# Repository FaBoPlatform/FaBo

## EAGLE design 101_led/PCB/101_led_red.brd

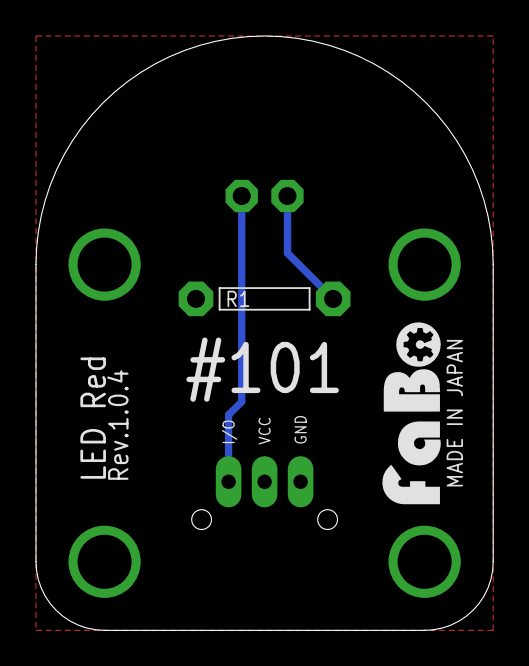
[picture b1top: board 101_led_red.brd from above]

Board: 2 copper layers, 25.4 x 33.0 mm, 5 parts (0 on the bottom side), 3 nets.

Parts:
J1: FABO_BRICK_3PIN
LED1: LED_5MM
R1: 1k; AXL-REGULAR
U$1: LOGO_FABO_MS
U$2: LOGO_OSHW_M_BOTTOM

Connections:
GND: J1.GND, R1.1
unnamed: J1.I/O, LED1.A
unnamed: LED1.K, R1.2

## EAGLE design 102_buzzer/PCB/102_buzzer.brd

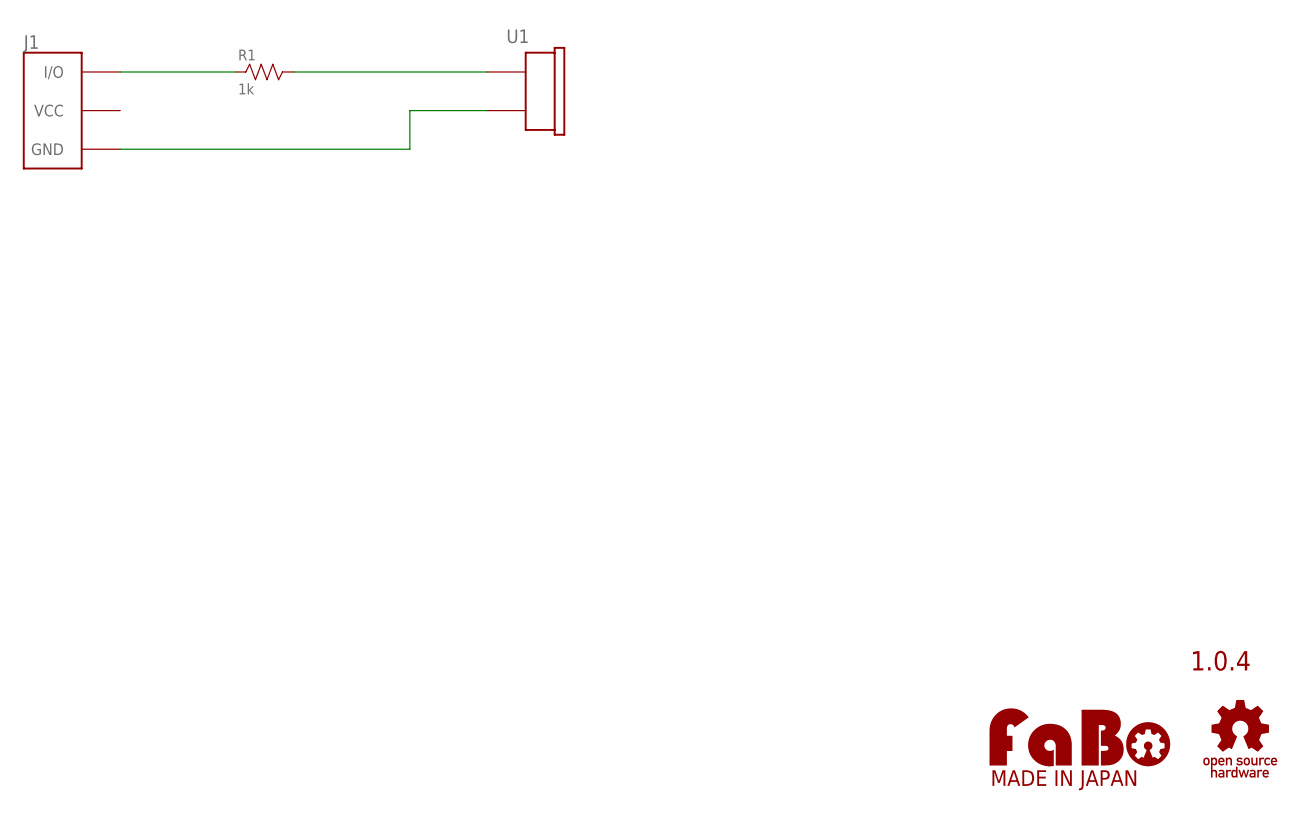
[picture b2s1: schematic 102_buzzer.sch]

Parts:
J1: FABO_BRICK_3PIN
R1: 1k; AXL-REGULAR
U1: BUZZER; PKM13EPYH4000-A0
U$2: LOGO_FABO-M; LOGO_FABO_MS
U$3: LOGO_OSHW-M_BOTTOM; LOGO_OSHW_M_BOTTOM

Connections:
GND: J1.GND, U1.2
unnamed: J1.I/O, R1.1
unnamed: R1.2, U1.1

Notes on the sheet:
1.0.4

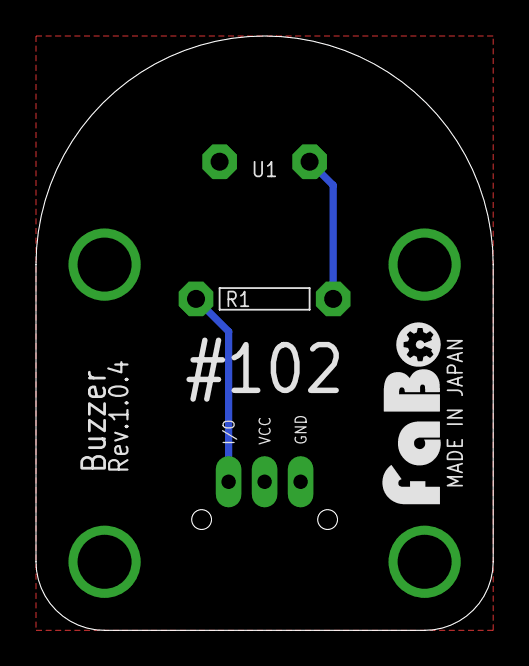
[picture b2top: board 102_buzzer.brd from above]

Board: 2 copper layers, 25.4 x 33.0 mm, 5 parts (0 on the bottom side), 3 nets.

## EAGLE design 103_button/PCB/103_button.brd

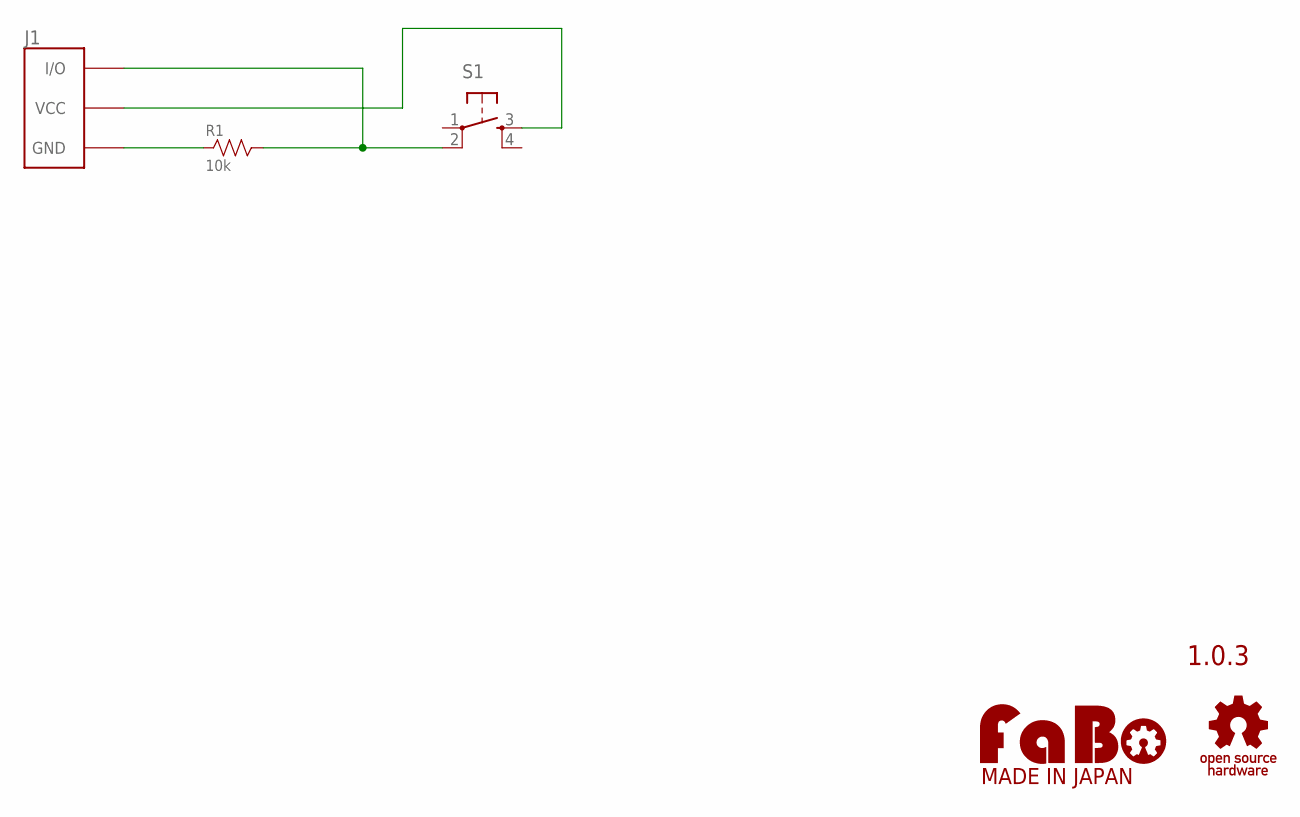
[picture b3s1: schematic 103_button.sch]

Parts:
J1: FABO_BRICK_3PIN
R1: 10k; AXL-REGULAR
S1: TACT-SWITCH-12MM; 1273HA-160G-G
U$2: LOGO_OSHW-M_BOTTOM; LOGO_OSHW_M_BOTTOM
U$3: LOGO_FABO-M_BOTTOM; LOGO_FABO_MS_BOTTOM

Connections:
GND: J1.GND, R1.1
unnamed: J1.VCC, S1.3
unnamed: J1.I/O, R1.2, S1.2

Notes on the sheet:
1.0.3

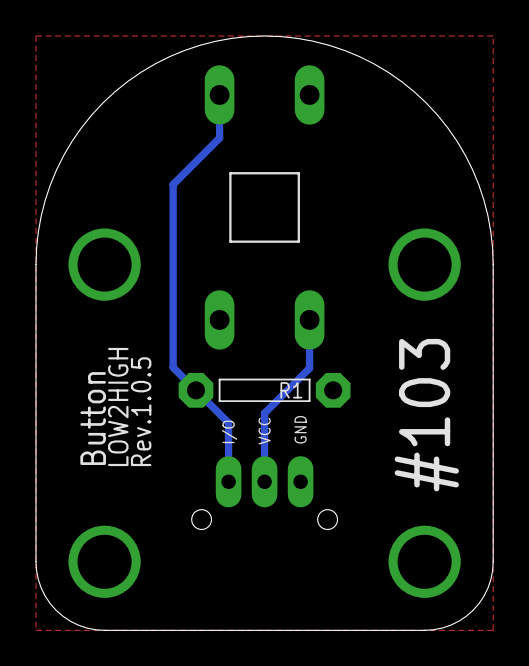
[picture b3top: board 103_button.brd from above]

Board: 2 copper layers, 25.4 x 33.0 mm, 5 parts (0 on the bottom side), 3 nets.

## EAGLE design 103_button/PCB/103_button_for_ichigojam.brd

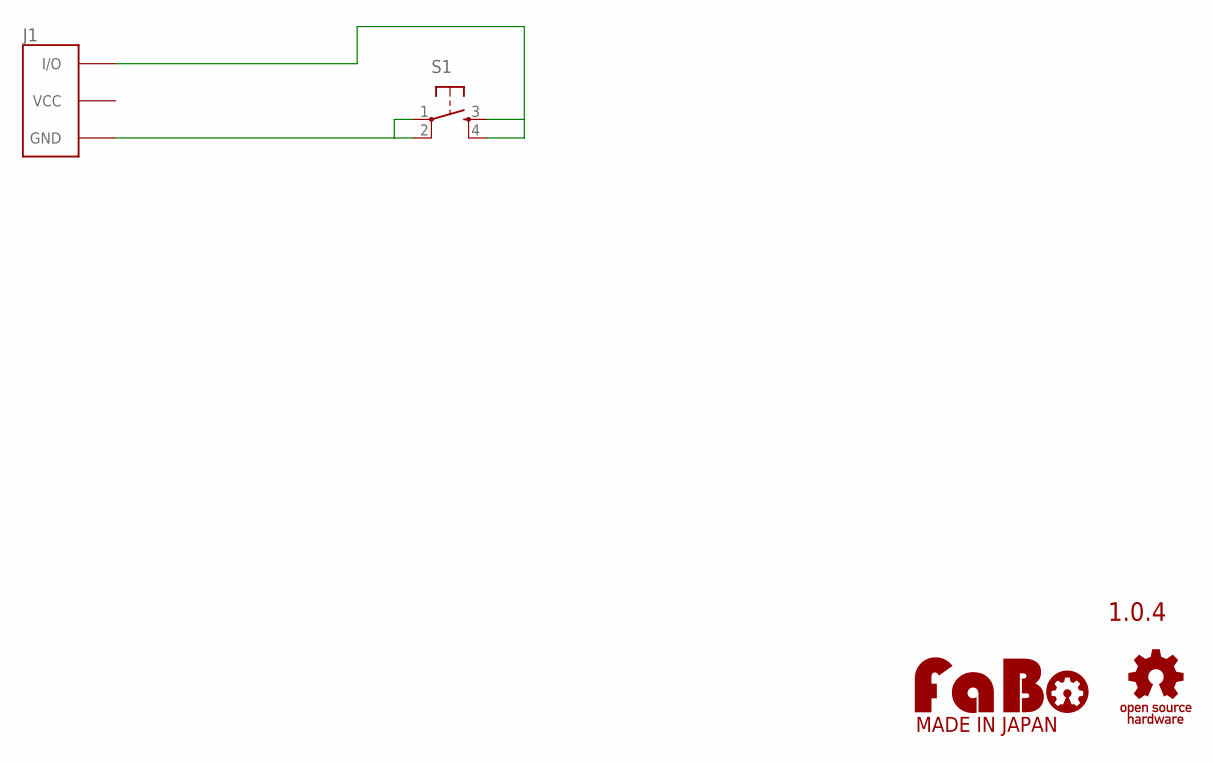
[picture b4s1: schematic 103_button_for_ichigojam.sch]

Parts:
J1: FABO_BRICK_3PIN
S1: TACT-SWITCH-12MM; 1273HA-160G-G
U$2: LOGO_OSHW-M_BOTTOM; LOGO_OSHW_M_BOTTOM
U$3: LOGO_FABO-M_BOTTOM; LOGO_FABO_MS_BOTTOM

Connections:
GND: J1.GND, S1.1, S1.2
unnamed: J1.I/O, S1.3, S1.4

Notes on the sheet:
1.0.4

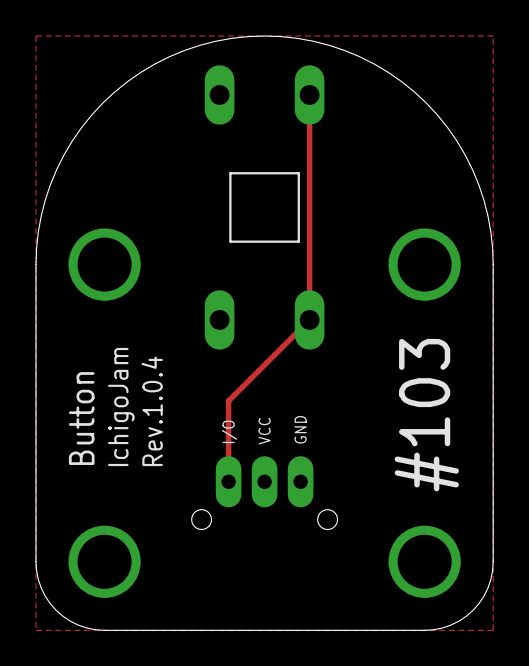
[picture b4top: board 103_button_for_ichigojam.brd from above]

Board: 2 copper layers, 25.4 x 33.0 mm, 4 parts (0 on the bottom side), 2 nets.

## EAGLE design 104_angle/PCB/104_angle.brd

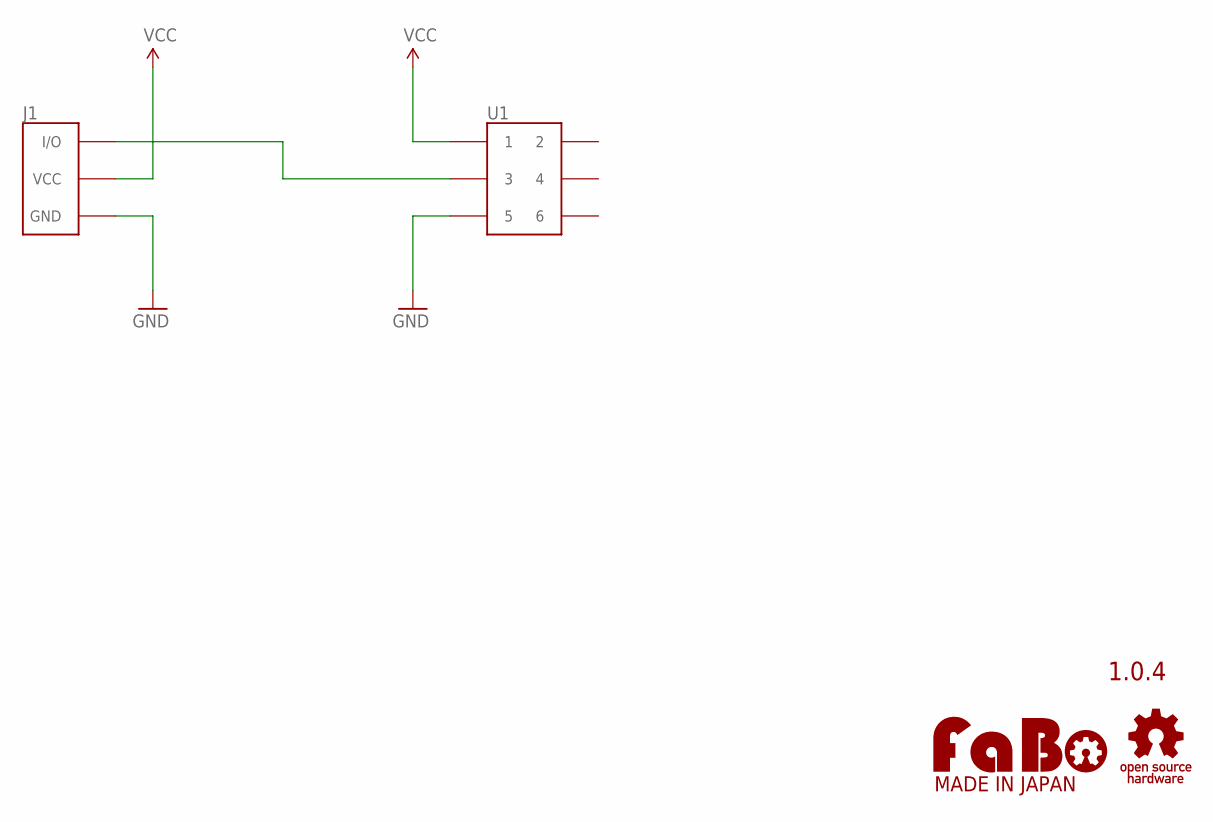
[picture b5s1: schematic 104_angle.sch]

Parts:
J1: FABO_BRICK_3PIN
U1: ROTARYENCORDER
U$2: LOGO_FABO-M; LOGO_FABO_MS
U$3: LOGO_OSHW-M_BOTTOM; LOGO_OSHW_M_BOTTOM

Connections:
GND: J1.GND, U1.5
unnamed: J1.I/O, U1.3
VCC: J1.VCC, U1.1

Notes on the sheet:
1.0.4

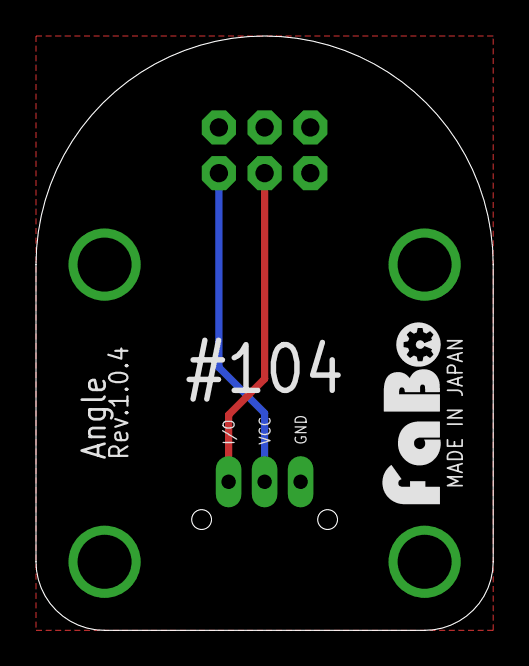
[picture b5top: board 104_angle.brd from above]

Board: 2 copper layers, 25.4 x 33.0 mm, 4 parts (0 on the bottom side), 3 nets.

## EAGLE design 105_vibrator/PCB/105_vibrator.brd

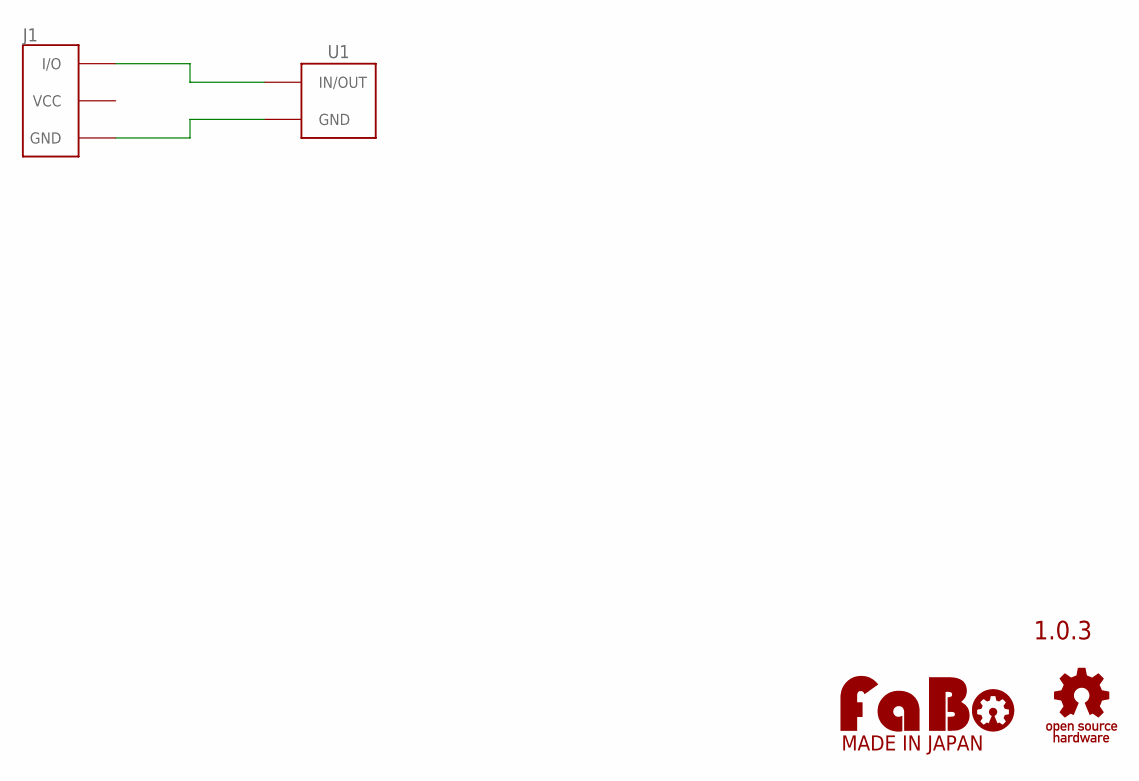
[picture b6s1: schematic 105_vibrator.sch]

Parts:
J1: FABO_BRICK_3PIN
U1: VIBRATOR; LA3R5-480AH1_PTH
U$2: LOGO_OSHW-M_BOTTOM; LOGO_OSHW_M_BOTTOM
U$3: LOGO_FABO-M; LOGO_FABO_MS

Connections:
GND: J1.GND, U1.P$2 (GND)
unnamed: J1.I/O, U1.P$1 (IN/OUT)

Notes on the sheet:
1.0.3

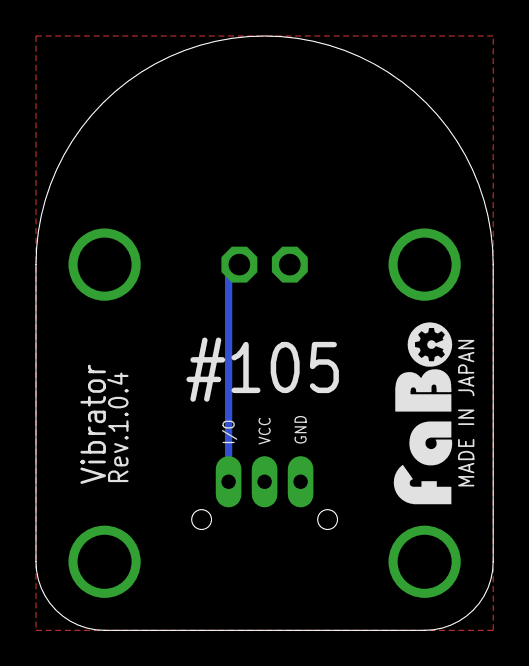
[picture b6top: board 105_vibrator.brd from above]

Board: 2 copper layers, 25.4 x 33.0 mm, 4 parts (0 on the bottom side), 2 nets.

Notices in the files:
parts and their libraries:
FaBo-etc: Released under the Creative Commons Attribution-ShareAlike 4.0 License
https://creativecommons.org/licenses/by-sa/4.0
FaBo-etc: Released under the Creative Commons
